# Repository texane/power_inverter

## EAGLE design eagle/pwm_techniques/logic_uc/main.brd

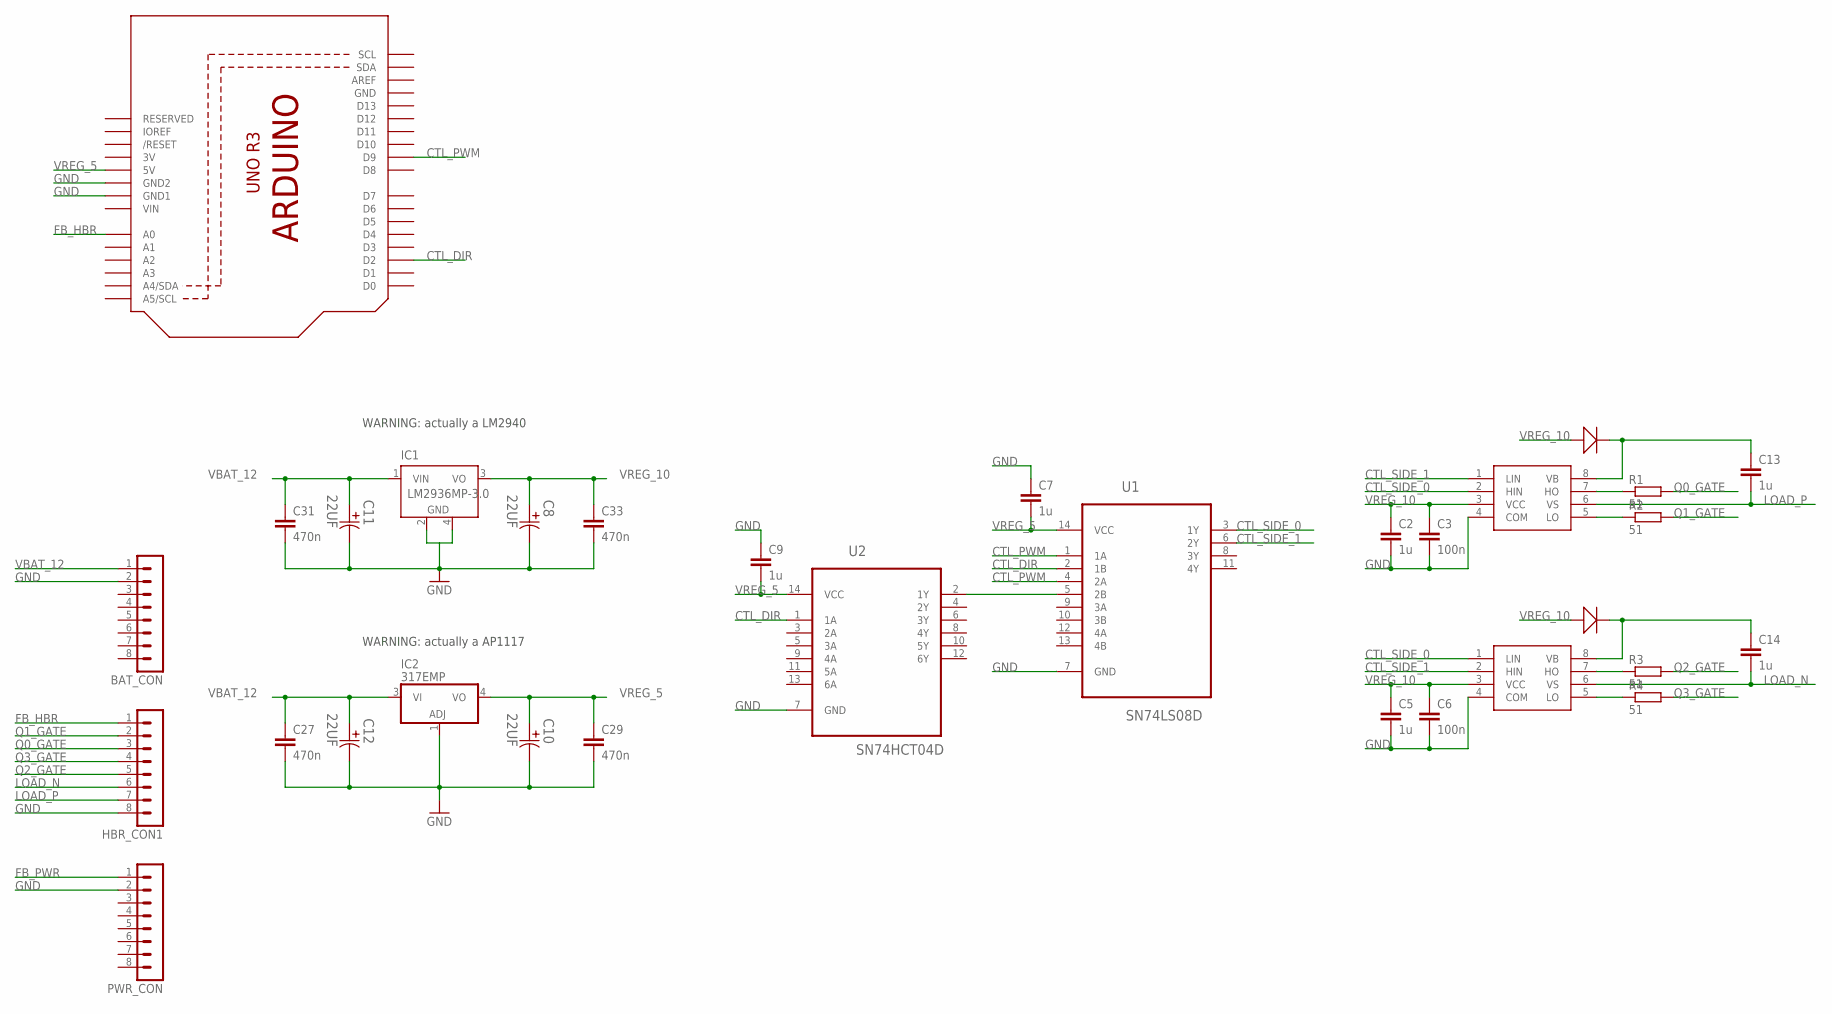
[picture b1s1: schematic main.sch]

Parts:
BAT_CON: MA08-1
C2, C5, C7, C9: 1u; C1206
C3, C6: 100n; C1206
C8, C10, C11, C12: 22UF; CAPAE660X610N
C13, C14: 1u; C2220K
C27, C29, C31, C33: 470n; C1206
HBR_CON1: MA08-1
IC1: LM2936MP-3.0; SOT223
IC2: 317EMP; SOT223
IR2304_0, IR2304_1: IR2304; SOIC8
PWR_CON: MA08-1
R1, R2, R3, R4: 51; M1206
U1: SN74LS08D; SOIC127P600X175-14N
U2: SN74HCT04D; SOIC127P600X175-14N
U3: ARDUINOR3-DIMENSION; ARDUINOR3
U$1, U$2: 1SR154; SOD106-W

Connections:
3V: U3.3V
CTL_DIR: U1.2 (1B), U2.1 (1A), U3.D2
CTL_PWM: U1.1 (1A), U1.4 (2A), U3.D9
CTL_SIDE_0: IR2304_0.2 (HIN), IR2304_1.1 (LIN), U1.3 (1Y)
CTL_SIDE_1: IR2304_0.1 (LIN), IR2304_1.2 (HIN), U1.6 (2Y)
FB_HBR: HBR_CON1.1, U3.A0
FB_PWR: PWR_CON.1
GND: BAT_CON.2, C2.2, C3.2, C5.2, C6.2, C7.1, C8.2, C9.1, C10.2, C11.2, C12.2, C27.2, C29.2, C31.2, C33.2, HBR_CON1.8, IC2.1 (ADJ), IR2304_0.4 (COM), IR2304_1.4 (COM), PWR_CON.2, U1.7 (GND), U2.7 (GND), U3.GND, U3.GND1, U3.GND2
LOAD_N: C14.2, HBR_CON1.6, IR2304_1.6 (VS)
LOAD_P: C13.2, HBR_CON1.7, IR2304_0.6 (VS)
unnamed: C13.1, IR2304_0.8 (VB), U$1.C
unnamed: C14.1, IR2304_1.8 (VB), U$2.C
unnamed: IR2304_0.7 (HO), R1.1
unnamed: IR2304_0.5 (LO), R2.1
unnamed: U1.5 (2B), U2.2 (1Y)
unnamed: IR2304_1.7 (HO), R3.1
unnamed: IR2304_1.5 (LO), R4.1
unnamed: IC1.2 (GND), IC1.4 (GND)
Q0_GATE: HBR_CON1.3, R1.2
Q1_GATE: HBR_CON1.2, R2.2
Q2_GATE: HBR_CON1.5, R3.2
Q3_GATE: HBR_CON1.4, R4.2
VBAT_12: BAT_CON.1, C11.1, C12.1, C27.1, C31.1, IC1.1 (VIN), IC2.3 (VI)
VIN: U3.VIN
VREG_5: C7.2, C9.2, C10.1, C29.1, IC2.4 (VO), U1.14 (VCC), U2.14 (VCC), U3.5V
VREG_10: C2.1, C3.1, C5.1, C6.1, C8.1, C33.1, IC1.3 (VO), IR2304_0.3 (VCC), IR2304_1.3 (VCC), U$1.A, U$2.A

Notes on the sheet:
WARNING: actually a LM2940
WARNING: actually a AP1117

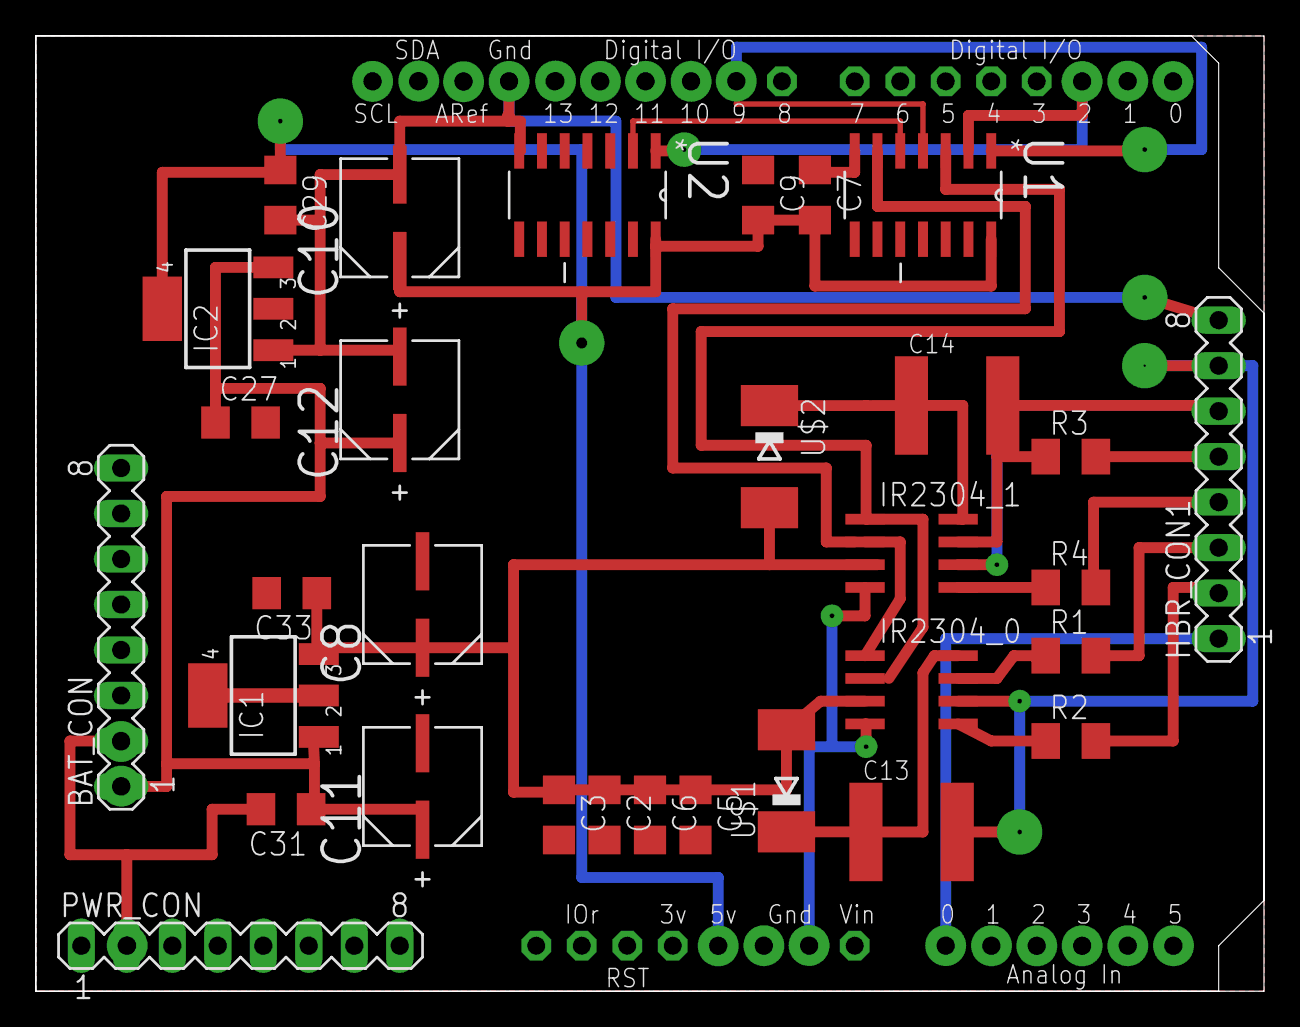
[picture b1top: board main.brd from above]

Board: 2 copper layers, 68.6 x 53.3 mm, 32 parts (0 on the bottom side), 23 nets.

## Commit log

2013-09-04 [ add ] eagle
2013-09-04 [ update ] add gain stage
2013-09-04 [ add ] tl494cd
2013-09-04 [ update ] pwm control stage, wip
2013-09-04 [ update ] logic schematics
2013-09-04 [ update ] logic schematics, connectors
2013-09-05 [ update ] pwm_techniques/power
2013-09-05 [ add ] pwm_techniques/logic/notes
2013-09-06 [ update ] logic: 50hz, tunable sine wave
2013-09-06 [ add ] ltspice/logic
2013-09-06 [ update ] ltspice/logic
2013-09-06 [ update ] todo, thermal paste
2013-09-07 [ update, add ] ltspice/logic. add lm358, tl084 models
2013-09-07 [ update, add ] ltspice/logic. add 1n4154 model
2013-09-07 [ add ] tl494 ltspice model
2013-09-07 [ add ] ltspice readme
2013-09-08 [ update ] test tl494 simulation
2013-09-08 [ update ] ltspice/logic whole circuit. not simulating.
2013-09-15 [ add ] src/spwm
2013-09-15 [ update ] spwm, unit testing
2013-09-15 [ update ] add atmega328p makefile, upload
2013-09-16 [ update ] spwm, major fixes
2013-09-16 [ fix ] TCNT1 automatically cleared
2013-09-18 [ update ] direction control
2013-09-18 [ update ] remove comments
2013-09-19 [ update ] add pwm exclusion logic
2013-09-19 [ update, add ] rename logic to logic_discrete, add logic_uc
2013-09-20 [ update ] use SOT223 for LDOs
2013-09-20 [ update ] todo: replace diode package is sod106
2013-09-20 [ add ] 1sr154.lbr, adafruit.lbr (for arduino uno)
2013-09-20 [ update ] logic_uc main schematics
2013-09-20 [ add ] logic_uc board
2013-09-20 [ update ] main.brd
2013-09-21 [ update ] logic_uc board routed
2013-09-21 [ update ] logic_uc, PCB printable version
2013-09-21 [ update, add ] logic_uc top layer fliped

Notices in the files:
parts and their libraries:
SparkFun: Licensing: CC v3.0 Share-Alike You are welcome to use this library for commercial purposes.
